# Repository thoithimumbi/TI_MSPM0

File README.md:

# Low-Power MSPM0 Sensor Node with USB-C Connectivity

## System Overview
The board is powered via a USB-C connector, providing a primary 5V rail which is regulated to 3.3V for the MCU and onboard peripherals.

The system integrates:
- A high-performance ARM Cortex-M0+ microcontroller  
- A USB-to-UART bridge for direct serial communication  
- A 3-axis accelerometer for motion sensing applications  

---

## Functional Blocks

### Power Management
- **Input:** +5V from USB VBUS  
- **Regulation:** SPX3819M5-L-3-3 LDO → 3.3V rail  
- **Filtering:**
  - 10 µF (bulk)
  - 470 nF (high-frequency bypass)

Decoupling capacitors are placed on both input and output stages to reduce noise and ensure rail stability.

---

### Microcontroller (TI MSPM0G3507)
The MSPM0G3507PTR (LQFP-48) serves as the central processing unit.

**Key configurations:**
- **Clocking:**  
  External 8 MHz crystal (X1) with 15 pF load capacitors for precise timing  

- **Programming & Debugging:**  
  TC2030 SWD header (SWDIO / SWCLK) for firmware flashing and real-time debugging  

- **Reset Circuit:**  
  - 5.1 kΩ pull-up resistor  
  - 470 nF capacitor for noise filtering  
  Ensures stable and reliable startup behavior  

---

### USB-to-UART Interface
- **IC:** CH340E USB-to-serial converter  
- **Function:** Bridges USB differential pair (D+ / D−) to MCU UART  

**Connections:**
- PA0 → TX  
- PA1 → RX  

**Protection:**
- USBLC6-2SC6 ESD diode array on USB lines  
- Safeguards against electrostatic discharge and hot-plug transients  

---

### Sensors & Peripherals

#### LIS2DH Accelerometer
A low-power, high-resolution 3-axis accelerometer integrated on the 3.3V domain.

- **Interface:** I2C  
  - SDA → PA10  
  - SCL → PA11  
  - Pull-ups: 5.1 kΩ  

- **Interrupts:**
  - INT1 → PB8  
  - INT2 → PB9  

Supports interrupt-driven operation, enabling:
- Motion-triggered events  
- Low-power sleep modes with wake-on-interrupt  

---

## Technical Specifications

| Component        | Description                                  |
|------------------|----------------------------------------------|
| MCU              | TI MSPM0G3507 (ARM Cortex-M0+, up to 80 MHz) |
| USB Connector    | USB-C (USB 2.0 Full Speed)                   |
| Interface IC     | CH340E USB-to-UART                           |
| Voltage Rails    | 5V (USB), 3.3V (LDO Output)                  |
| Accelerometer    | LIS2DH (3-axis)                              |
| I2C Address      | Configurable via hardware                    |
| PCB Features     | 4× M3 mounting holes, 3× fiducials           |

---

## Connectivity Table (Key Signals)

| Function  | MCU Pin | Peripheral     |
|----------|--------|----------------|
| UART TX  | PA0    | CH340E RXD     |
| UART RX  | PA1    | CH340E TXD     |
| I2C SDA  | PA10   | LIS2DH SDA     |
| I2C SCL  | PA11   | LIS2DH SCL     |
| SWDIO    | PA19   | TC2030 (Pin 2) |
| SWCLK    | PA20   | TC2030 (Pin 4) |

---

## Design Notes
- External crystal ensures accurate UART baud rates and I2C timing  
- Interrupt-driven accelerometer minimizes power consumption  
- USB ESD protection improves reliability in real-world usage  
- Tag-Connect header reduces footprint while maintaining debug access  

---

## Media

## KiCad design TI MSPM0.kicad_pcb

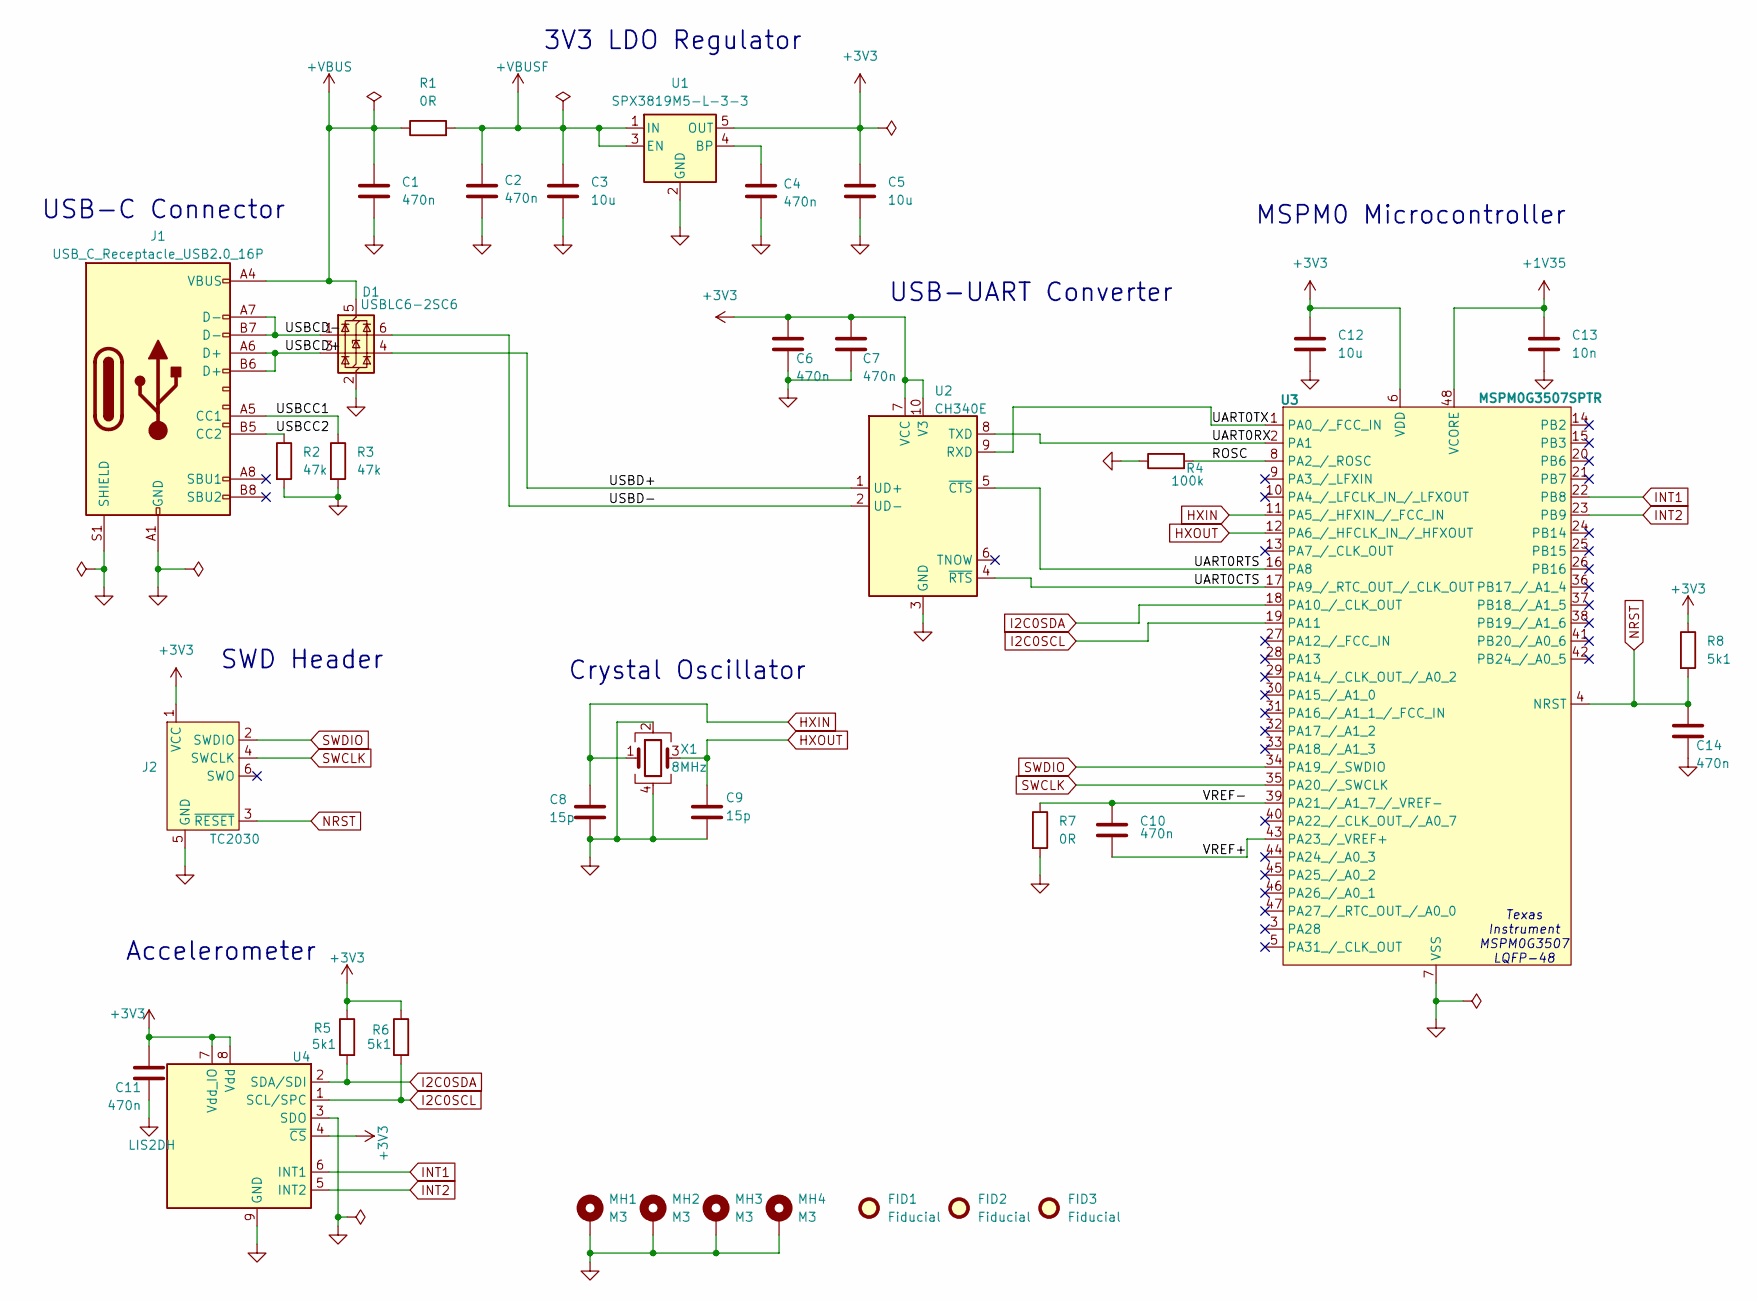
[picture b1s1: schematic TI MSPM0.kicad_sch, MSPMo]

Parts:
C1, C2, C4, C6, C7, C10, C11, C14: 470n; C_0603_1608Metric
C3, C5, C12: 10u; C_0603_1608Metric
C8, C9: 15p; C_0603_1608Metric
C13: 10n; C_0201_0603Metric
D1: USBLC6-2SC6; SOT-23-6
FID1, FID2, FID3: Fiducial; Fiducial_1mm_Mask2mm
J1: USB_C_Receptacle_USB2.0_16P; USB_C_Receptacle_GCT_USB4105-xx-A_16P_TopMnt_Horizontal
J2: TC2030; Tag-Connect_TC2030-IDC-FP_2x03_P1.27mm_Vertical
MH1, MH2, MH3, MH4: M3; MountingHole_3.2mm_M3_Pad_Via
R1, R7: 0R; R_0603_1608Metric
R2, R3: 47k; R_0603_1608Metric
R4: 100k; R_0603_1608Metric
R5, R6, R8: 5k1; R_0603_1608Metric
U1: SPX3819M5-L-3-3; SOT-23-5
U2: CH340E; MSOP-10_3x3mm_P0.5mm
U3: MSPM0G3507SPTR; LQFP-48_7x7mm_P0.5mm
U4: LIS2DH; LGA-14_2x2mm_P0.35mm_LayoutBorder3x4y
X1: 8MHz; Crystal_SMD_3225-4Pin_3.2x2.5mm

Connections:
+1V35: C13.1, U3.48 (VCORE)
+3V3: C5.1, C6.1, C7.1, C11.1, C12.1, J2.1 (VCC), R5.1, R6.1, R8.1, U1.5 (OUT), U2.7 (VCC), U2.10 (V3), U3.6 (VDD), U4.4 (~CS), U4.7 (Vdd_IO), U4.8 (Vdd)
+VBUS: C1.1, D1.5 (VBUS), J1.A4 (VBUS), J1.A9 (VBUS), J1.B4 (VBUS), J1.B9 (VBUS), R1.1
+VBUSF: C2.1, C3.1, R1.2, U1.1 (IN), U1.3 (EN)
/ROSC: R4.2, U3.8 (PA2_/_ROSC)
/UART0CTS: U2.4 (~RTS), U3.17 (PA9_/_RTC_OUT_/_CLK_OUT)
/UART0RTS: U2.5 (~CTS), U3.16 (PA8)
/UART0RX: U2.8 (TXD), U3.2 (PA1)
/UART0TX: U2.9 (RXD), U3.1 (PA0_/_FCC_IN)
/USBCC1: J1.A5 (CC1), R3.1
/USBCC2: J1.B5 (CC2), R2.1
/USBCD+: D1.3 (I/O2), J1.A6 (D+), J1.B6 (D+)
/USBCD-: D1.1 (I/O1), J1.A7 (D-), J1.B7 (D-)
/USBD+: D1.4 (I/O2), U2.1 (UD+)
/USBD-: D1.6 (I/O1), U2.2 (UD-)
/VREF+: C10.2, U3.43 (PA23_/_VREF+)
/VREF-: C10.1, R7.1, U3.39 (PA21_/_A1_7_/_VREF-)
GND: C1.2, C2.2, C3.2, C4.2, C5.2, C6.2, C7.2, C8.2, C9.2, C11.2, C12.2, C13.2, C14.2, D1.2 (GND), J1.A1 (GND), J1.A12 (GND), J1.B1 (GND), J1.B12 (GND), J1.S1 (SHIELD), J2.5 (GND), MH1.1, MH2.1, MH3.1, MH4.1, R2.2, R3.2, R4.1, R7.2, U1.2 (GND), U2.3 (GND), U3.7 (VSS), U4.3 (SDO), U4.9 (GND), U4.10 (GND), U4.11 (GND), U4.12 (GND), U4.13 (GND), U4.14 (GND), X1.2, X1.4
HXIN: C8.1, U3.11 (PA5_/_HFXIN_/_FCC_IN), X1.1
HXOUT: C9.1, U3.12 (PA6_/_HFCLK_IN_/_HFXOUT), X1.3
I2C0SCL: R6.2, U3.19 (PA11), U4.1 (SCL/SPC)
I2C0SDA: R5.2, U3.18 (PA10_/_CLK_OUT), U4.2 (SDA/SDI)
INT1: U3.22 (PB8), U4.6 (INT1)
INT2: U3.23 (PB9), U4.5 (INT2)
NRST: C14.1, J2.3 (~RESET), R8.2, U3.4 (NRST)
unnamed: C4.1, U1.4 (BP)
SWCLK: J2.4 (SWCLK), U3.35 (PA20_/_SWCLK)
SWDIO: J2.2 (SWDIO), U3.34 (PA19_/_SWDIO)

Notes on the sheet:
USB-C Connector
SWD Header
Crystal Oscillator
3V3 LDO Regulator
MSPM0 Microcontroller
Accelerometer
USB-UART Converter
Texas Instrument MSPM0G3507 LQFP-48

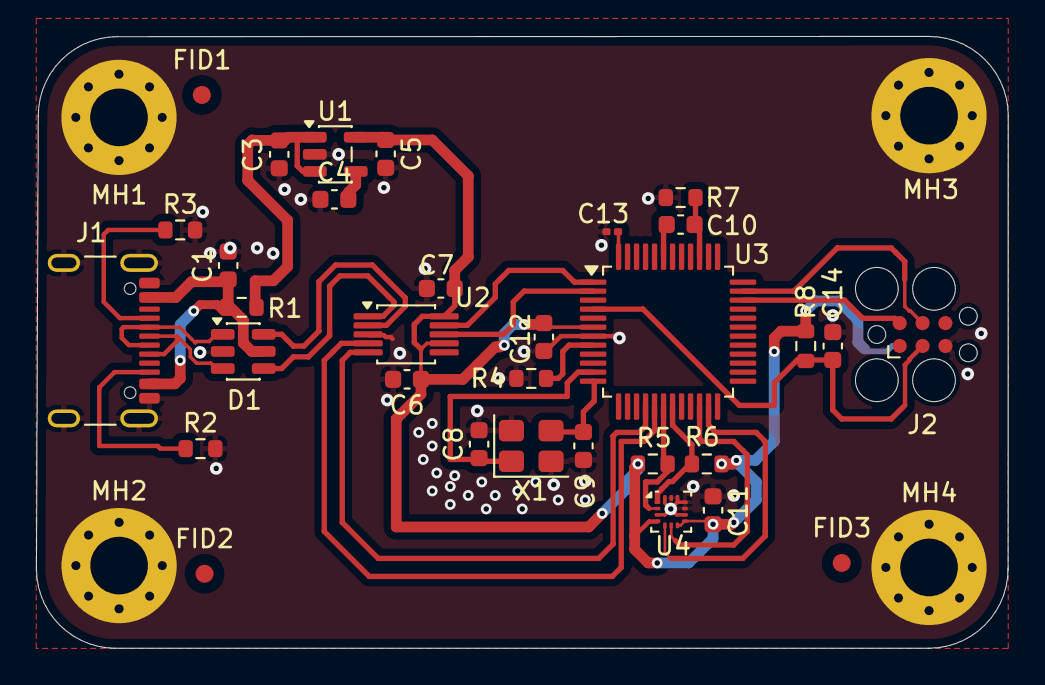
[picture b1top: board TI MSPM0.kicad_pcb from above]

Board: 2 copper layers, 54.0 x 34.0 mm, 36 parts (0 on the bottom side), 28 nets.

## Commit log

2026-03-02 Add README.md for MSPM0-Based USB Development Board
2026-03-03 Add preview section with 3D image
    Add a preview section with a 3D image to the README.
2026-03-03 Fix image link formatting in README.md
2026-03-03 Update image reference in README
2026-03-03 Add PNG schematic image to README
    Added a PNG version of the schematic to the README.
2026-03-03 Update image in README from schematic to 3D
2026-03-03 Fix image source in README.md
2026-03-03 Fix image source path in README.md
